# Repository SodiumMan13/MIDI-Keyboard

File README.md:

# MIDI-Keyboard
A MIDI keyboard with capacitive touch keys, sliders, push switches, and a rotary encoder

I made this MIDI keyboard for the 3rd week of Half-Life. It has 8 capacitive touch keys, 2 slider potentiometers, 3 key switches, and a rotary encoder. The PCB is 99x99 mm. 

These are the schematics:

This is the PCB:

This is the render:

and the back:

The parts can be sourced from Digi-Key, AliExpress, and JLCPCB. The total will be about 30 dollars from those.

For the firmware, you can use CircuitPython for the Waveshare ESP32-S3 Zero. This article explains what you can do: https://github.com/KMKfw/kmk_firmware/blob/main/docs/en/Getting_Started.md

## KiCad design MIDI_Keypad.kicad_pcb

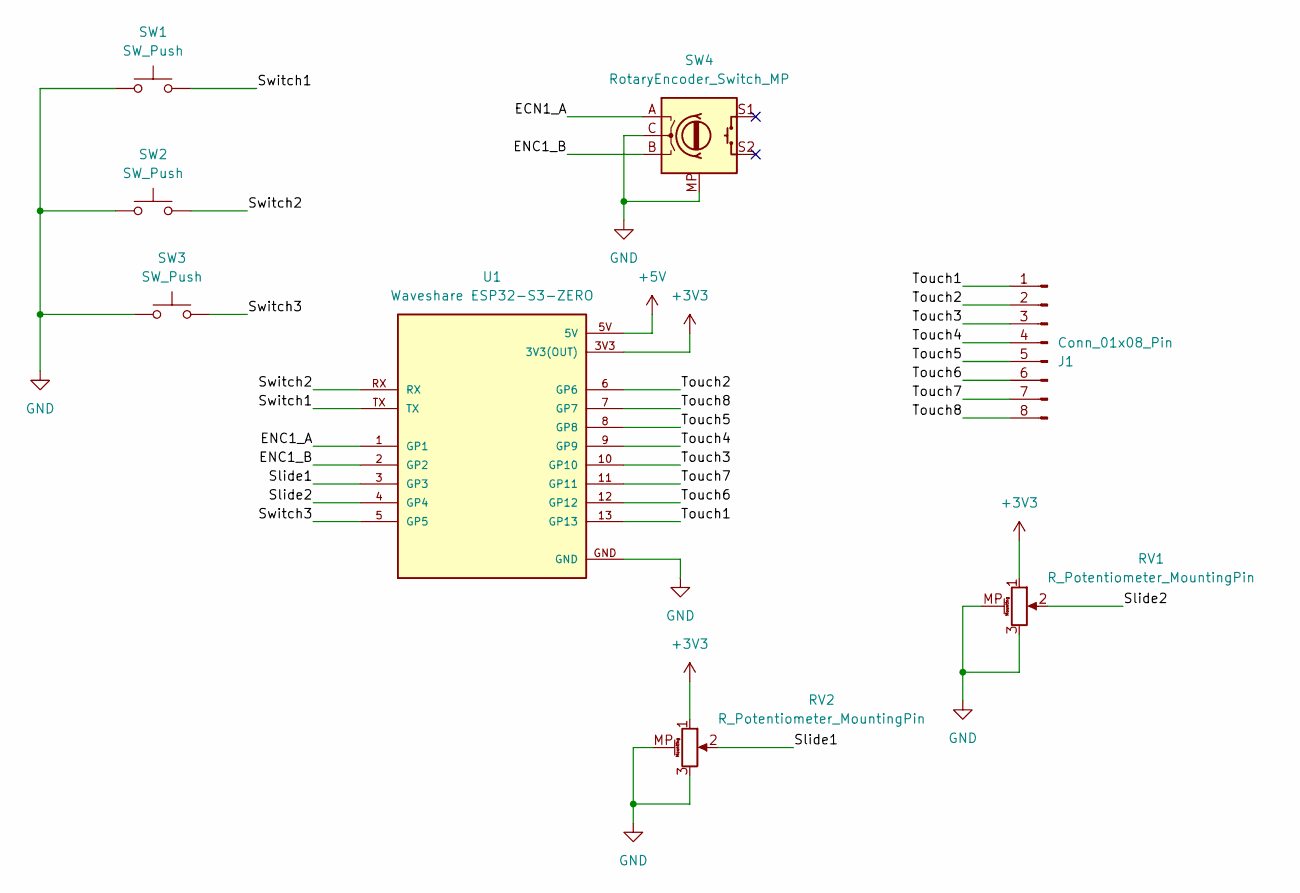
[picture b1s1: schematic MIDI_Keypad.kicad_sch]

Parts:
J1: Conn_01x08_Pin; MIDI keys
RV1, RV2: R_Potentiometer_MountingPin; Potentiometer_Bourns_PTA1543_Single_Slide
SW1, SW2, SW3: SW_Push; Kailh Choc Low-Profile Switches
SW4: RotaryEncoder_Switch_MP; RotaryEncoder_Alps_EC11E-Switch_Vertical_H20mm
U1: Waveshare ESP32-S3-ZERO; Waveshare ESP32-S3-Zero; PARTREV NA

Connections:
+3V3: RV1.1, RV2.1, U1.3V3 (3V3(OUT))
+5V: U1.5V
/ECN1_A: SW4.A
/ENC1_A: U1.1 (GP1)
/ENC1_B: SW4.B, U1.2 (GP2)
/Slide1: RV2.2, U1.3 (GP3)
/Slide2: RV1.2, U1.4 (GP4)
/Switch1: SW1.2, U1.TX
/Switch2: SW2.2, U1.RX
/Switch3: SW3.2, U1.5 (GP5)
/Touch1: J1.1, U1.13 (GP13)
/Touch2: J1.2, U1.6 (GP6)
/Touch3: J1.3, U1.10 (GP10)
/Touch4: J1.4, U1.9 (GP9)
/Touch5: J1.5, U1.8 (GP8)
/Touch6: J1.6, U1.12 (GP12)
/Touch7: J1.7, U1.11 (GP11)
/Touch8: J1.8, U1.7 (GP7)
GND: RV1.3, RV1.MP (MountPin), RV2.3, RV2.MP (MountPin), SW1.1, SW2.1, SW3.1, SW4.C, SW4.MP, U1.GND

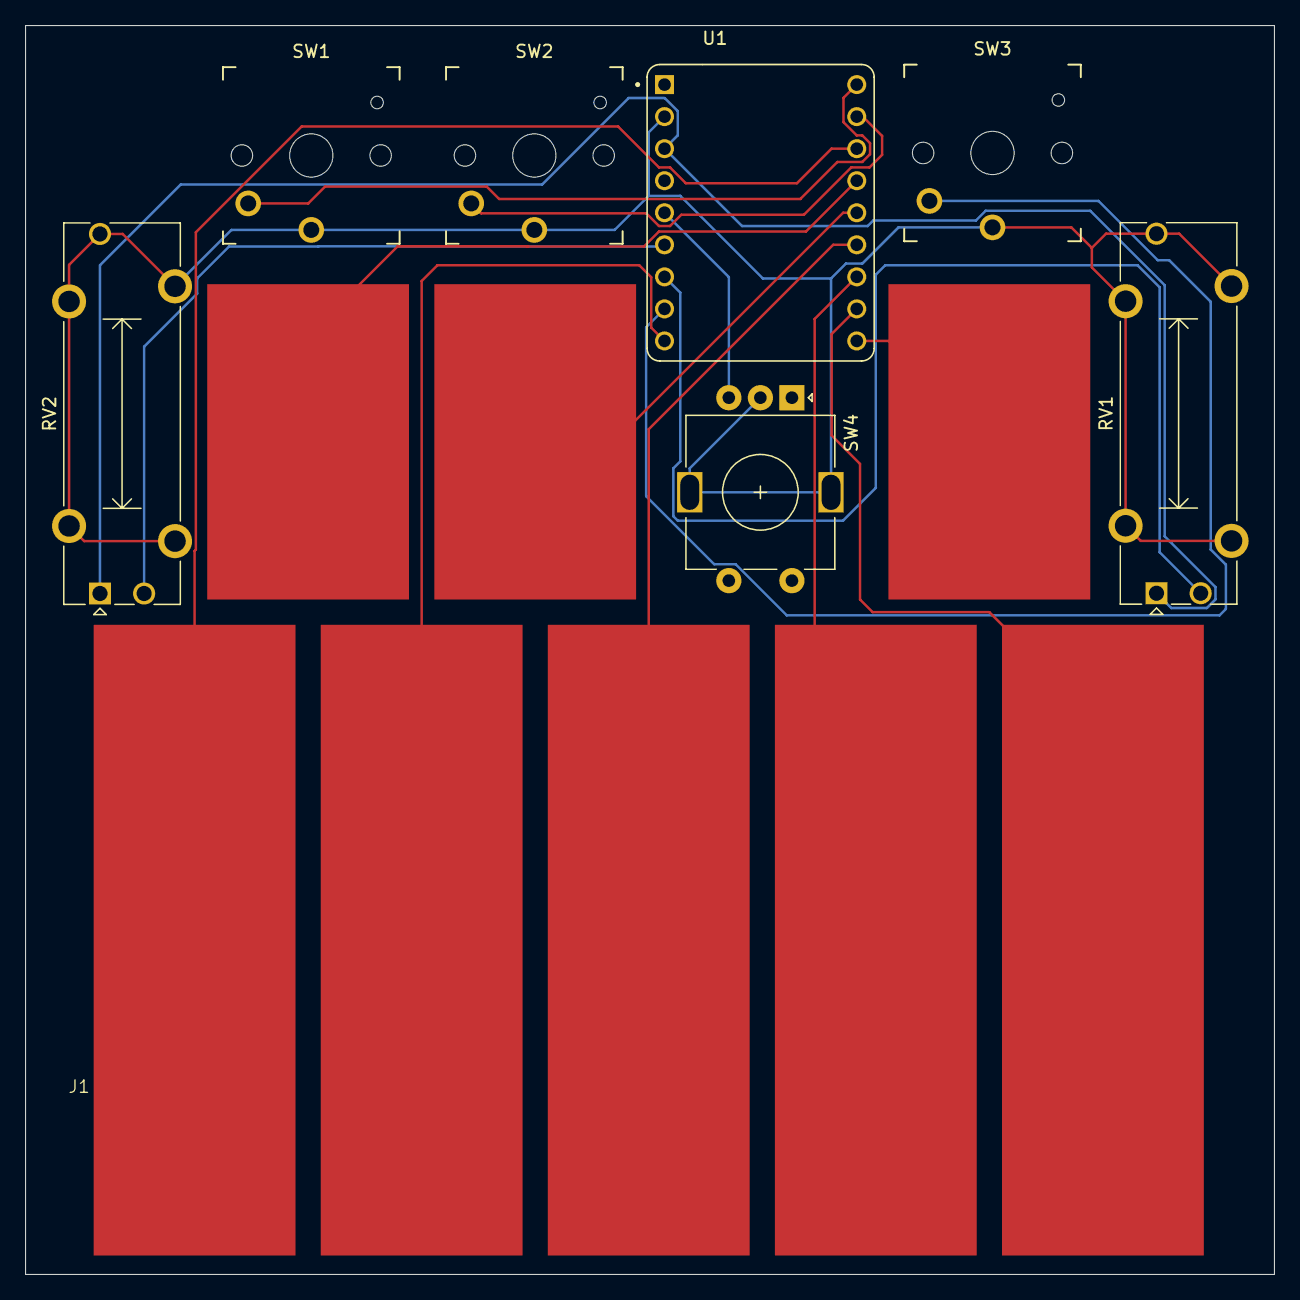
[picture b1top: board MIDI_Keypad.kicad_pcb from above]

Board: 2 copper layers, 99.0 x 99.0 mm, 8 parts (0 on the bottom side), 16 nets.
